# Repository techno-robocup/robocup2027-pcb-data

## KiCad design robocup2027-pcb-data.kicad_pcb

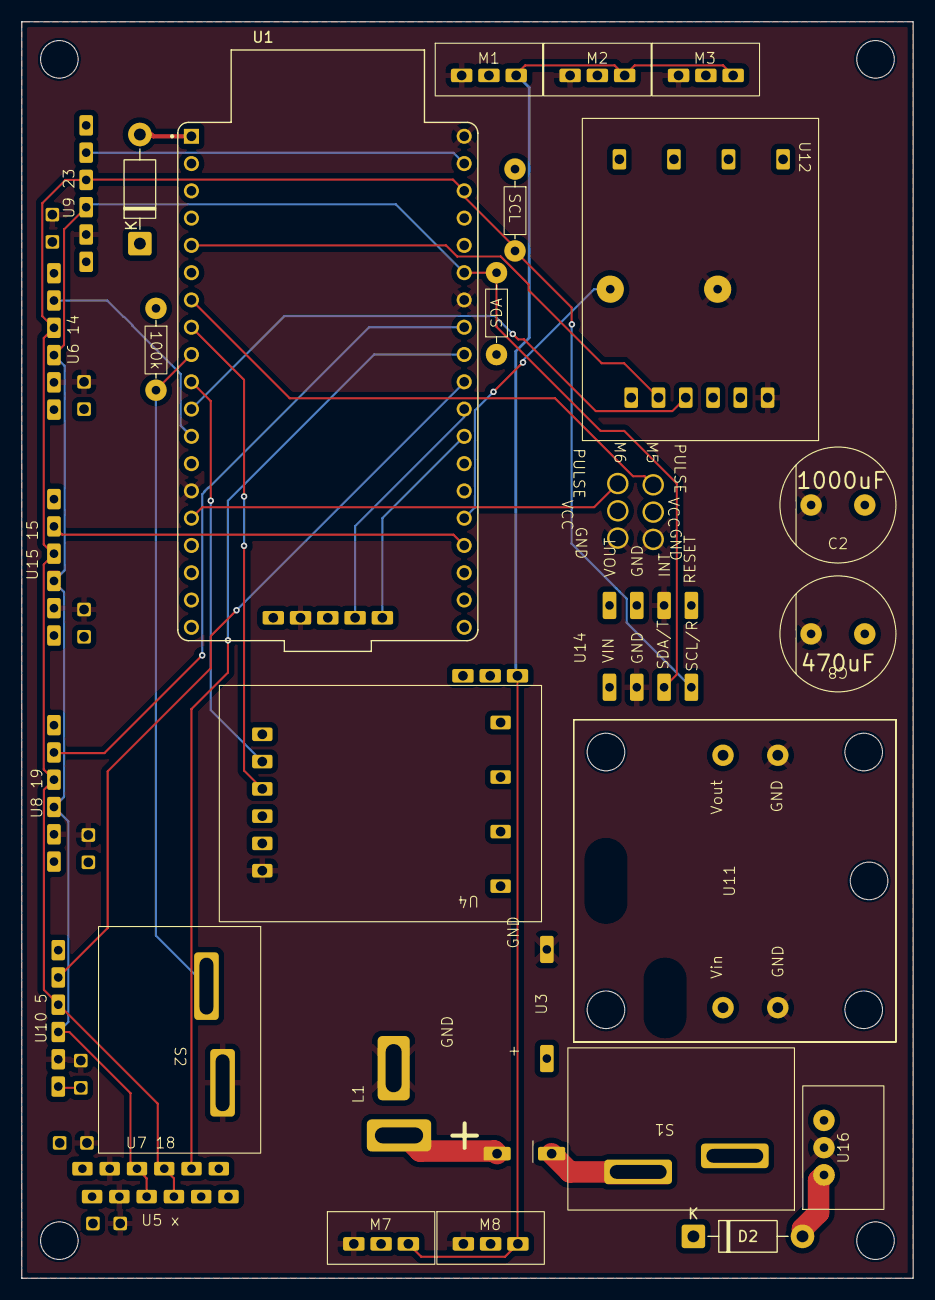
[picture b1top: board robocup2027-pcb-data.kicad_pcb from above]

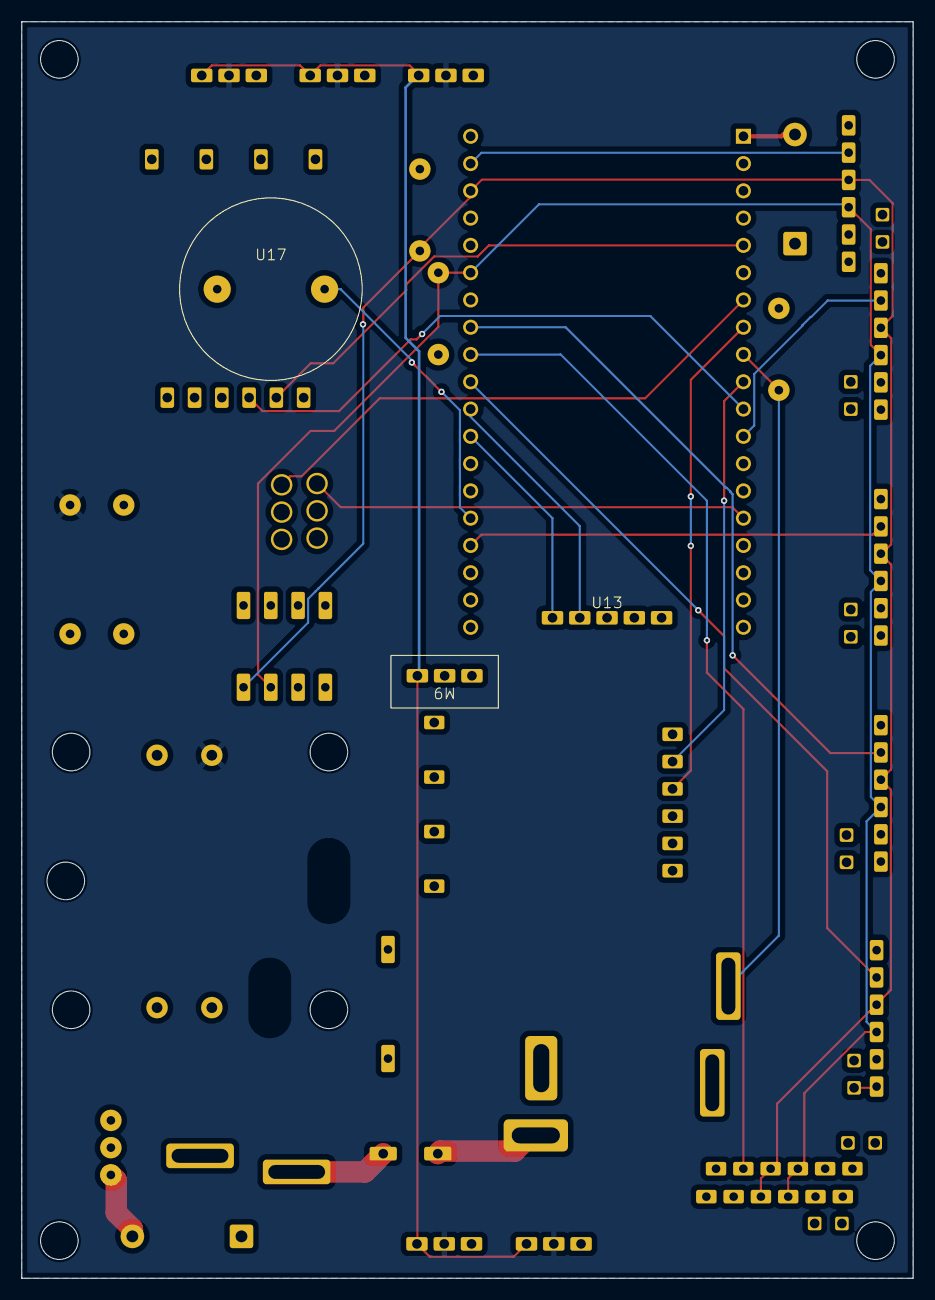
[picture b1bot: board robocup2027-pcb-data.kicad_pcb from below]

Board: 4 copper layers, 83.0 x 117.0 mm, 42 parts (3 on the bottom side), 27 nets.

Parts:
C1, C3, C4, C5, C6, C7, C9: 0.1uF; 2.54mm_capacitor
C2: 1000uF; capacitor
C8: 470uF; capacitor
D1, D2: 1N4001; D_DO-41_SOD81_P10.16mm_Horizontal
F1: Fuse; 5.08mm_capacitor_1
L1: LiPo
M1, M2, M3, M7, M8, M9: sts3032
M5, M6: Motor_Servo; servo_motor_3
R1, R2: 8.4k; Resister
R3: 100k; Resister
S1, S2: tactile switch; CW-SB11KKFF
U1: ESP32-DEVKITC-32E; MODULE_ESP32-DEVKITC-32E
U3: voltmeter
U4, U12: AE-HX711
U5 x, U6 14, U7 18, U8 19, U9 23, U10 5, U15 15: VL53L1X-ToF
U11: DCDC-LTC3111
U13: fe-urt-2
U14: AE-BNO055-BO
U16: DCDC-M78AR033-0.5
U17: PKM13EPYH4000-A0

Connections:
+3.3V: C1.1, C3.1, C4.1, C5.1, C6.1, C7.1, C8.1, C9.1, D1.1 (K), D2.1 (K), M5.2 (+), M6.2 (+), R1.1, R2.1, R3.1, U4.5 (VDD), U5 x.1 (V+), U6 14.1 (V+), U7 18.1 (V+), U8 19.1 (V+), U9 23.1 (V+), U10 5.1 (V+), U12.5 (VDD), U13.3 (5V), U14.1 (VIN), U15 15.1 (V+)
+6V: C2.1, M1.2 (VCC), M2.2 (VCC), M3.2 (VCC), M7.2 (VCC), M8.2 (VCC), U11.3 (Vout)
Debug: U1.J3_15 (IO2), U17.2 (VCC)
FE-URT-2-RXD: U1.J3_11 (IO17), U13.2 (RXD)
FE-URT-2-TXD: U1.J3_12 (IO16), U13.1 (TXD)
GND: C1.2, C2.2, C3.2, C4.2, C5.2, C6.2, C7.2, C8.2, C9.2, L1.2 (-), M1.1 (GND), M2.1 (GND), M3.1 (GND), M5.3 (-), M6.3 (-), M7.1 (GND), M8.1 (GND), S2.2, U1.J2_14 (GND_J2_14), U1.J3_1 (GND_J3_1), U1.J3_7 (GND_J3_7), U3.2 (GND), U4.10 (GND), U5 x.2 (GND), U6 14.2 (GND), U7 18.2 (GND), U8 19.2 (GND), U9 23.2 (GND), U10 5.2 (GND), U11.2 (GND), U11.4 (GND), U12.10 (GND), U13.4 (GND), U14.2 (GND), U14.7 (GND), U15 15.2 (GND), U16.2 (GND), U17.1 (GND)
I2C_SCL: R1.2, U1.J3_3 (IO22), U5 x.4 (SCL), U6 14.4 (SCL), U7 18.4 (SCL), U8 19.4 (SCL), U9 23.4 (SCL), U10 5.4 (SCL), U14.4 (SCL/R), U15 15.4 (SCL)
I2C_SDA: R2.2, U1.J3_6 (IO21), U5 x.3 (SDA), U6 14.3 (SDA), U7 18.3 (SDA), U8 19.3 (SDA), U9 23.3 (SDA), U10 5.3 (SDA), U14.3 (SDA/T), U15 15.3 (SDA)
LiPo+: S1.1, U3.1 (+), U11.1 (Vin), U16.1 (+Vin)
unnamed: D1.2 (A), U1.J2_1 (3V3)
unnamed: D2.2 (A), U16.3 (+Vout)
unnamed: F1.2, S1.2
unnamed: F1.1, L1.1 (+)
unnamed: R3.2, S2.1, U1.J2_9 (IO25)
SG90_1_SIG: M5.1 (PWM), U1.J2_7 (IO32)
SG90_2_SIG: M6.1 (PWM), U1.J2_15 (IO13)
STS3032_signal: M1.3 (Signal), M2.3 (Signal), M3.3 (Signal), M7.3 (Signal), M8.3 (Signal), M9.3 (Signal)
XSHUT1: U1.J2_12 (IO14), U6 14.5 (XSHUT)
XSHUT2: U1.J3_9 (IO18), U7 18.5 (XSHUT)
XSHUT3: U1.J3_8 (IO19), U8 19.5 (XSHUT)
XSHUT4: U1.J3_2 (IO23), U9 23.5 (XSHUT)
XSHUT5: U1.J3_10 (IO5), U10 5.5 (XSHUT)
XSHUT6: U1.J3_16 (IO15), U15 15.5 (XSHUT)
load1_CLK: U1.J2_8 (IO33), U4.7 (CLK)
load1_DAT: U1.J2_10 (IO26), U4.6 (DAT)
load2_CLK: U1.J2_11 (IO27), U12.7 (CLK)
load2_DAT: U1.J2_5 (IO34), U12.6 (DAT)

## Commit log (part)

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2026-04-10 new pcb data
    Created the 6V power supply
2026-04-13 new data
2026-04-13 updating schematics
2026-04-14 end of the day
2026-04-17 done with schematics
2026-04-17 update stuff
2026-04-20 update library
2026-04-21 adding an appropriate gitignore
2026-04-21 updating footprints
2026-04-21 assigning footprints
2026-04-21 assigned all footprints except the motors
2026-04-21 removing gitignore files
2026-04-21 fixed footprint
2026-05-22 done with the schematics
2026-05-22 assigned footprint
2026-05-22 placed stuff
2026-05-23 fixing extra pins to match with footprints
2026-05-23 assigned footprints and added them to pcb
2026-05-23 done with the placing
2026-05-23 generated step file
2026-05-23 changed to body only
2026-05-25 placing bno550
2026-05-27 removed dimension
2026-05-29 updating pcb and step file
2026-05-29 some changes
2026-06-01 fix: add vias and replace gyro
2026-06-01 edit print
2026-06-02 add debug speaker
2026-06-02 replaced photoreflector
2026-06-02 finished tracing
2026-06-04 refactor
2026-06-05 created fab
2026-06-06 removed all tracks
2026-06-06 changed copper layers to 4
2026-06-06 routed all parts
2026-06-08 Revert "aa"
    This reverts commit 22313cb6dd9aa4cc3fe09da59ca5f9739234b612.
2026-06-08 Revert "aa"
    This reverts commit 0866f59d12a45da3da4310fd215192e9ff9ddfa8.
2026-06-08 Revert "fix"
    This reverts commit b1364b1fb7fffef3f8b92053ebb4b15dbee0d99b.
2026-06-08 Revert "routed all parts"
    This reverts commit defdc4962c8a6b80579d15f30b626fadb053d299.
2026-06-08 ref silkprint
2026-06-08 fix pim
2026-06-08 asdf
2026-06-08 aaaa
2026-06-09 two ground layers
2026-06-09 regenerated data
